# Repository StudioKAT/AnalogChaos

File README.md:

# Analog Chaos

## 概要 / Overview

**Analog Chaos**は、2HPサイズの電圧制御可能なJerk Chaos CVジェネレーターです。

アナログ回路のフィードバックが生み出す、決定論的でありながら不規則な変化が特徴です。パッチに「偶然のようで、どこか連続性のある」揺らぎを加えます。

相互に関連しながら異なる表情を見せるX・Y・Zの3つのCV出力を搭載。複数のパラメーターを同時に変調することで、つながりのある複雑な動きを作り出せます。

変化の速度はRateノブと外部CVで調整でき、超低速域からLFO領域まで対応します。ゆっくりと移り変わる音色から、不規則なうねりまで、幅広いモジュレーションに活用できます。

基板上には、動きの性質を調整する4つの半固定抵抗を備えています。  
- Damp：振動を抑える帰還の強さを調整します。動きの勢いや収まり方に関わります。
- Gain：信号を回路へ戻す帰還の利得を調整します。出力音量ではなく、カオスを生み出すループの働きに関わります。
- Mod：回路内部に加える直流バイアスを調整します。動作の中心をずらすことで、揺らぎの偏りや動き方を変化させます。
- NL Drive：ダイオードによる非線形帰還の強さを調整します。波形の折れ曲がり方や、不規則な動きの生じ方に関わります。

これらは互いに影響し合い、設定によって不規則な揺らぎから周期的な動き、変化が収まる状態まで、振る舞いが変化します。

---

**Analog Chaos** is a voltage-controlled jerk chaos CV generator in a compact 2HP Eurorack format.

Feedback within its analog circuitry produces behavior that is deterministic yet irregular, adding fluctuations to your patch that feel unpredictable while retaining a sense of continuity.

Three CV outputs—X, Y, and Z—provide distinct but interrelated signals. Modulate multiple parameters simultaneously to create complex, connected movement throughout your patch.

The Rate knob and external CV input control the speed of these changes, covering a range from ultra-slow movement to LFO rates. From gradually evolving timbres to irregular swells, Analog Chaos offers a wide range of modulation possibilities.

Four trimmers on the circuit board let you adjust the character of the movement:

- **Damp:** Adjusts the strength of the feedback that damps oscillation, influencing how vigorously the circuit moves and how its motion settles.
- **Gain:** Adjusts the gain of the feedback loop that generates chaos, shaping the circuit’s behavior rather than directly setting the output level.
- **Mod:** Adjusts an internal DC bias, shifting the circuit’s operating point to change the balance and character of its fluctuations.
- **NL Drive:** Adjusts the strength of the nonlinear feedback through the diodes, influencing how the waveform bends and how irregular movement develops.

These controls interact with one another. Depending on their settings, the circuit can move between chaotic fluctuations, periodic oscillation, and a settled state.

## 仕様 / Spec
- Format: Eurorack
- Function: Chaos
- Current needs: +12V: 25mA, -12V: 25mA
- Width: 2 HP
- Depth: 36mm (including power connector)

## 販売 / Sales

StudioKATオフィシャルショップで販売しています。(日本国内限定)  
https://www.studiokat.jp/items/164466150

## ライセンス / License

この作品は [Creative Commons 表示 - 継承 4.0 国際 (CC BY-SA 4.0)](https://creativecommons.org/licenses/by-sa/4.0/deed.ja) の下でライセンスされています。  
This work is licensed under the [Creative Commons Attribution-ShareAlike 4.0 International License](https://creativecommons.org/licenses/by-sa/4.0/).

## クレジット / Credits

- Designed by : StudioKAT
- Website : https://www.studiokat.jp/
- GitHub : https://github.com/StudioKAT
- X(Twitter) : https://x.com/StudioKAT_synth
- Instagram : https://www.instagram.com/studiokat_modular/

## 更新履歴 / Changelog

- `2026-10-30` v2.0 Released version 2.0
- `2026-07-05` v1.0 Released version 1.0

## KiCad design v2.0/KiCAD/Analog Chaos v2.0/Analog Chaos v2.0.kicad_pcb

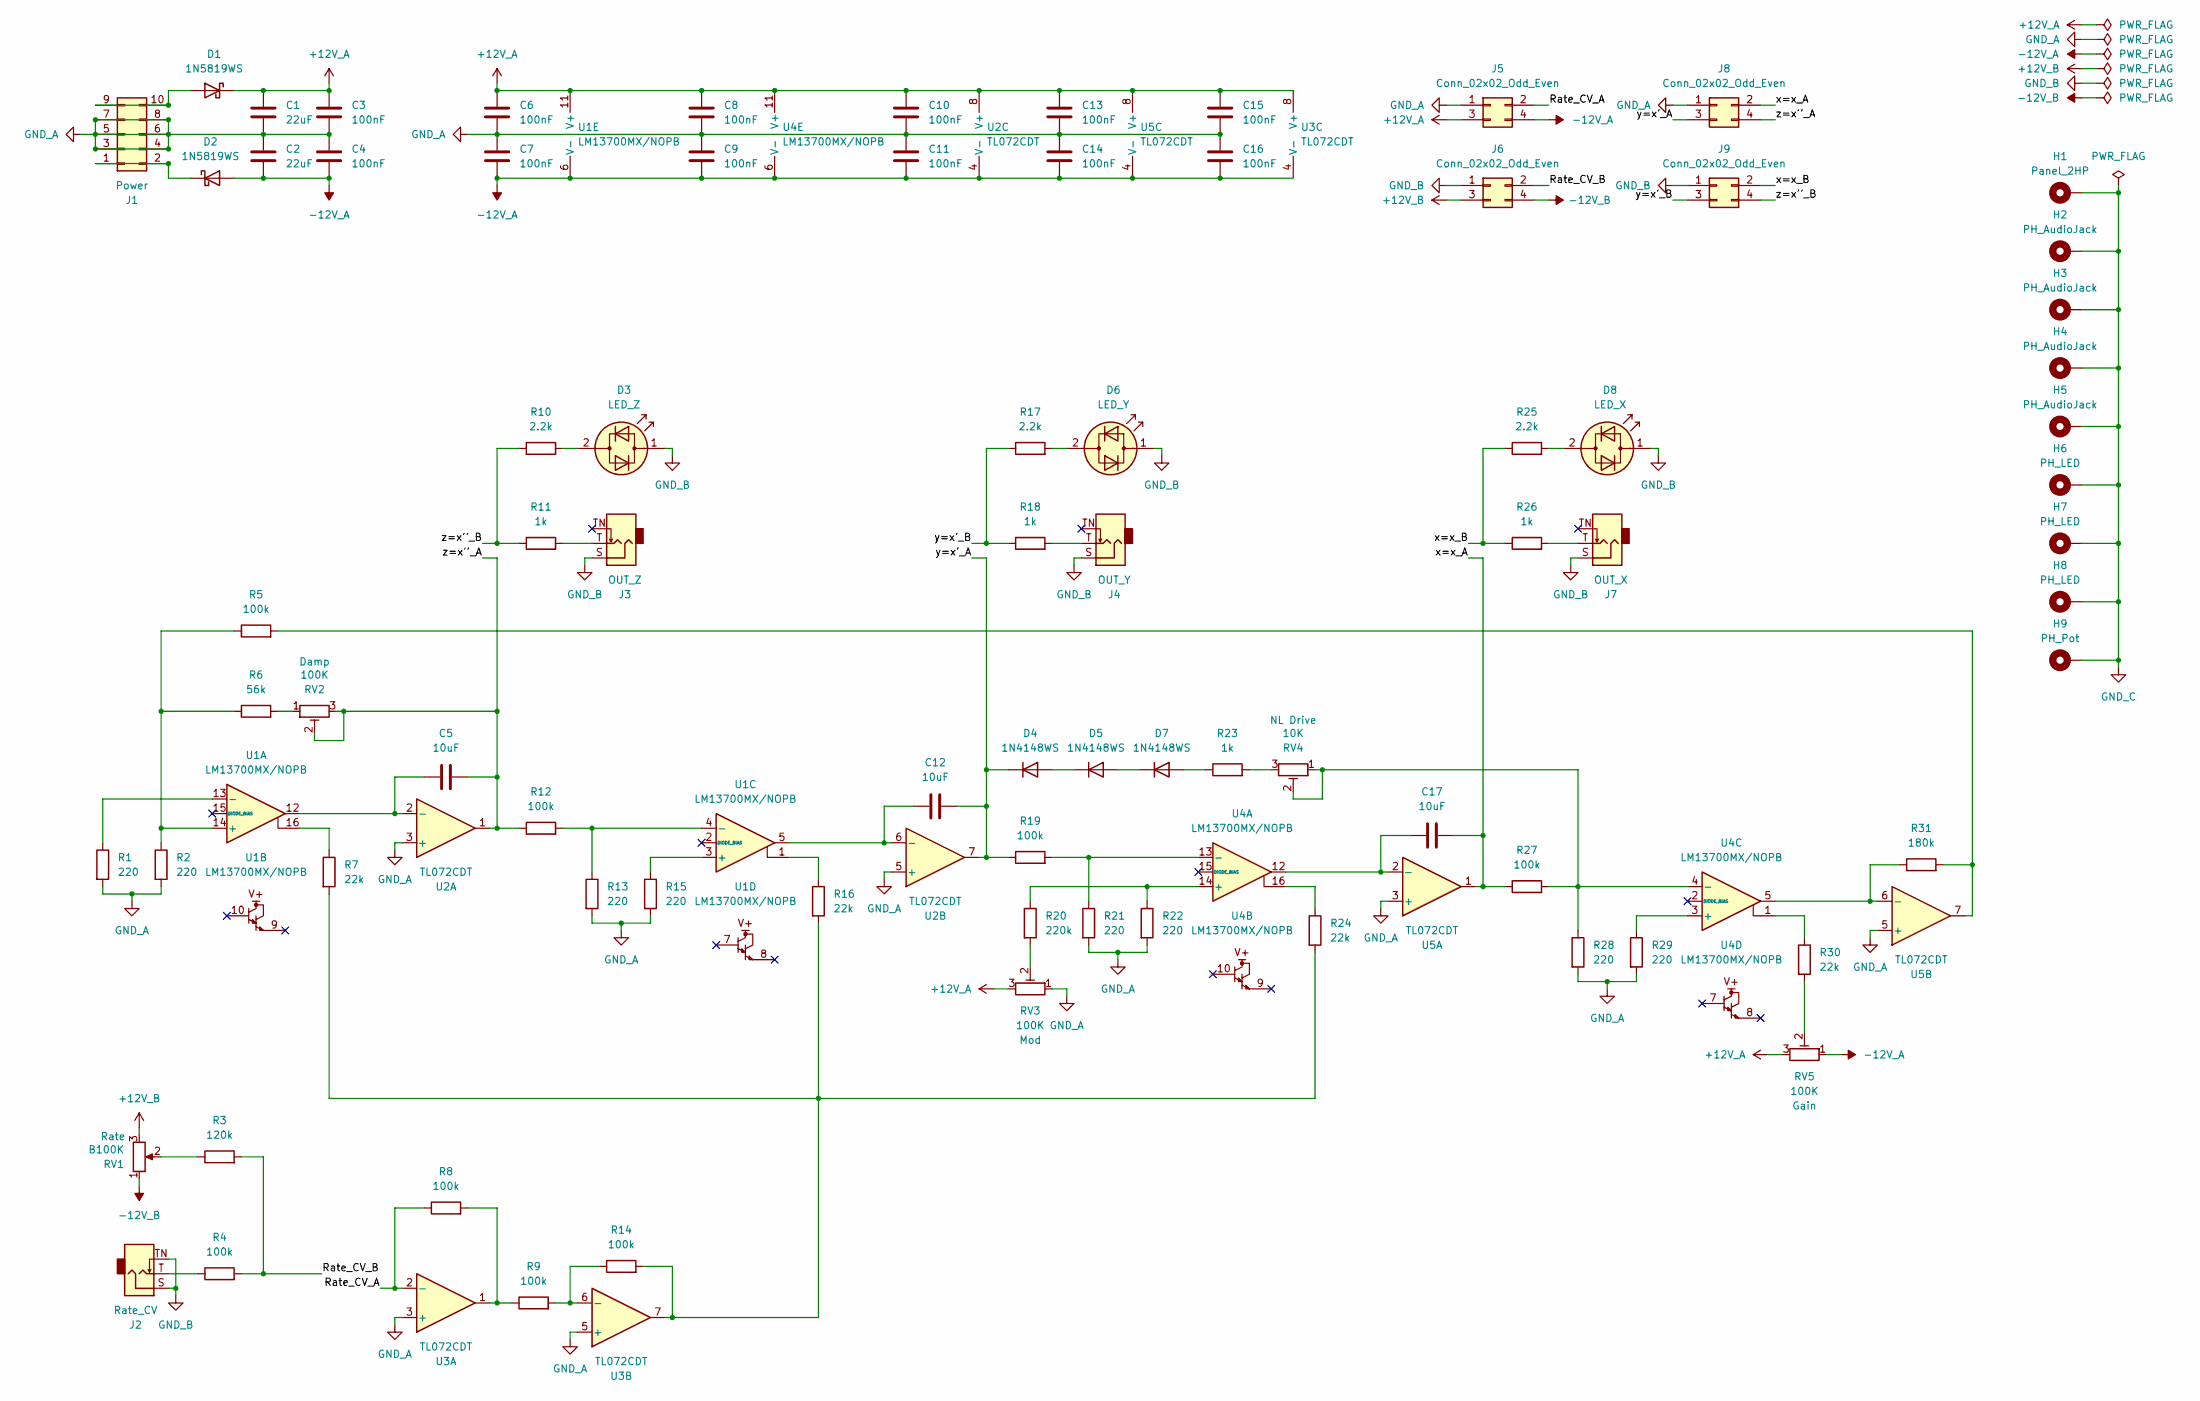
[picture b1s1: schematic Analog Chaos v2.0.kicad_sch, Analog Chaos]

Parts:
C1, C2: 22uF; C_0805_2012Metric; Voltage 25V; Tolerance ±20%; MFR Part CL21A226MAQNNNE; JLC Type Basic
C3, C4, C6, C7, C8, C9, C10, C11, C13, C14, C15, C16: 100nF; C_0603_1608Metric; Voltage 50V; Tolerance ±10%; MFR Part CC0603KRX7R9BB104; JLC Type Basic
C5, C12, C17: 10uF; C_0603_1608Metric; Voltage 25V; Tolerance ±20%; MFR Part CL10A106MA8NRNC; JLC Type Basic
D1, D2: 1N5819WS; D_SOD-323; MFR Part 1N5819WS; JLC Type Basic
D3: LED_Z; LED_D3.0mm_Clear
D4, D5, D7: 1N4148WS; D_SOD-323; MFR Part 1N4148WS; JLC Type Basic
D6: LED_Y; LED_D3.0mm_Clear
D8: LED_X; LED_D3.0mm_Clear
H1: Panel_2HP
H2, H3, H4, H5: PH_AudioJack; PH_AudioJack_3.5mm_Pad
H6, H7, H8: PH_LED; PH_LED_3.0mm_Pad
H9: PH_Pot; PH_RV09
J1: Power; IDC-Header_2x05_P2.54mm_Horizontal_SMD_EuroPower
J2: Rate_CV; Jack_3.5mm_QingPu_WQP-PJ398SM
J3: OUT_Z; Jack_3.5mm_QingPu_WQP-PJ398SM
J4: OUT_Y; Jack_3.5mm_QingPu_WQP-PJ398SM
J5, J8: Conn_02x02_Odd_Even; PinHeader_2x02_P2.54mm_Stand_SMD
J6, J9: Conn_02x02_Odd_Even; PinHeader_2x02_P2.54mm_Vertical_SMD
J7: OUT_X; Jack_3.5mm_QingPu_WQP-PJ398SM
R1, R2, R13, R15, R21, R22, R28, R29: 220; R_0603_1608Metric; Tolerance ±1%; MFR Part 0603WAF2200T5E; JLC Type Basic
R3: 120k; R_0603_1608Metric; Tolerance ±1%; MFR Part 0603WAF1203T5E; JLC Type Basic
R4, R5, R8, R9, R12, R14, R19, R27: 100k; R_0603_1608Metric; Tolerance ±1%; MFR Part 0603WAF1003T5E; JLC Type Basic
R6: 56k; R_0603_1608Metric; Tolerance ±1%; MFR Part 0603WAF5602T5E; JLC Type Basic
R7, R16, R24, R30: 22k; R_0603_1608Metric; Tolerance ±1%; MFR Part 0603WAF2202T5E; JLC Type Basic
R10, R17, R25: 2.2k; R_0603_1608Metric; Tolerance ±1%; MFR Part 0603WAF2201T5E; JLC Type Basic
R11, R18, R23, R26: 1k; R_0603_1608Metric; Tolerance ±1%; MFR Part 0603WAF1001T5E; JLC Type Basic
R20: 220k; R_0603_1608Metric; Tolerance ±1%; MFR Part 0603WAF2203T5E; JLC Type Basic
R31: 180k; R_0603_1608Metric; Tolerance ±1%; MFR Part 0603WAF1803T5E; LCSC C22827
RV1: B100K; Potentiometer_RV09
RV2, RV3, RV5: 100K; Potentiometer_Vishay_T73YP_Vertical
RV4: 10K; Potentiometer_Vishay_T73YP_Vertical
U1, U4: LM13700MX/NOPB; SOIC-16_3.9x9.9mm_P1.27mm; LCSC C174050
U2, U3, U5: TL072CDT; SOIC-8_3.9x4.9mm_P1.27mm; MFR Part TL072CDT; JLC Type Basic

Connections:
+12V_A: C1.1, C3.1, C6.1, C8.1, C10.1, C13.1, C15.1, D1.1 (K), J5.3, RV3.3, RV5.3, U1.11 (V+), U2.8 (V+), U3.8 (V+), U4.11 (V+), U5.8 (V+)
+12V_B: J6.3, RV1.3
-12V_A: C2.2, C4.2, C7.2, C9.2, C11.2, C14.2, C16.2, D2.2 (A), J5.4, RV5.1, U1.6 (V-), U2.4 (V-), U3.4 (V-), U4.6 (V-), U5.4 (V-)
-12V_B: J6.4, RV1.1
/Rate_CV_A: J5.2, R8.1, U3.2 (-)
/Rate_CV_B: J6.2, R3.2, R4.2
/x=x_A: C17.2, J8.2, R27.1, U5.1
/x=x_B: J9.2, R25.1, R26.1
/y=x'_A: C12.2, D4.1 (K), J8.3, R19.1, U2.7
/y=x'_B: J9.3, R17.1, R18.1
/z=x''_A: C5.2, J8.4, R12.1, RV2.2, RV2.3, U2.1
/z=x''_B: J9.4, R10.1, R11.1
GND_A: C1.2, C2.1, C3.2, C4.1, C6.2, C7.1, C8.2, C9.1, C10.2, C11.1, C13.2, C14.1, C15.2, C16.1, J1.3, J1.4, J1.5, J1.6, J1.7, J1.8, J5.1, J8.1, R1.2, R2.2, R13.2, R15.2, R21.2, R22.2, R28.2, R29.2, RV3.1, U2.3 (+), U2.5 (+), U3.3 (+), U3.5 (+), U5.3 (+), U5.5 (+)
GND_B: D3.1 (KA), D6.1 (KA), D8.1 (KA), J2.S, J2.TN, J3.S, J4.S, J6.1, J7.S, J9.1
GND_C: H1.1 (1_1), H2.1 (1_1), H3.1 (1_1), H4.1 (1_1), H5.1 (1_1), H6.1 (1_1), H7.1 (1_1), H8.1 (1_1), H9.1 (1_1)
unnamed: D1.2 (A), J1.9, J1.10
unnamed: D2.1 (K), J1.1, J1.2
unnamed: D3.2 (AK), R10.2
unnamed: D4.2 (A), D5.1 (K)
unnamed: D5.2 (A), D7.1 (K)
unnamed: D6.2 (AK), R17.2
unnamed: D7.2 (A), R23.1
unnamed: D8.2 (AK), R25.2
unnamed: J2.T, R4.1
unnamed: J3.T, R11.2
unnamed: J4.T, R18.2
unnamed: J7.T, R26.2
unnamed: R3.1, RV1.2
unnamed: R6.2, RV2.1
unnamed: R7.1, U1.16
unnamed: R8.2, R9.1, U3.1
unnamed: R7.2, R14.2, R16.2, R24.2, U3.7
unnamed: R16.1, U1.1
unnamed: R20.2, RV3.2
unnamed: R23.2, RV4.3
unnamed: R24.1, U4.16
unnamed: R30.1, U4.1
unnamed: R30.2, RV5.2
unnamed: R5.2, R31.2, U5.7
unnamed: R2.1, R5.1, R6.1, U1.14 (+)
unnamed: R1.1, U1.13 (-)
unnamed: R15.1, U1.3 (+)
unnamed: R12.2, R13.1, U1.4 (-)
unnamed: C5.1, U1.12, U2.2 (-)
unnamed: C12.1, U1.5, U2.6 (-)
unnamed: R9.2, R14.1, U3.6 (-)
unnamed: R20.1, R22.1, U4.14 (+)
unnamed: R19.2, R21.1, U4.13 (-)
unnamed: R29.1, U4.3 (+)
unnamed: R27.2, R28.1, RV4.1, RV4.2, U4.4 (-)
unnamed: C17.1, U4.12, U5.2 (-)
unnamed: R31.1, U4.5, U5.6 (-)

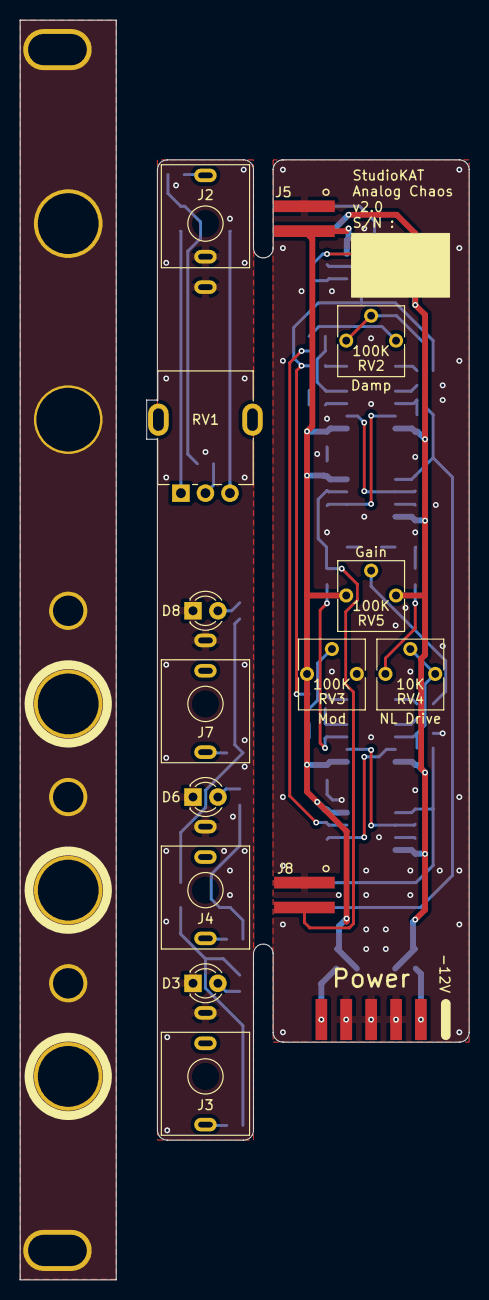
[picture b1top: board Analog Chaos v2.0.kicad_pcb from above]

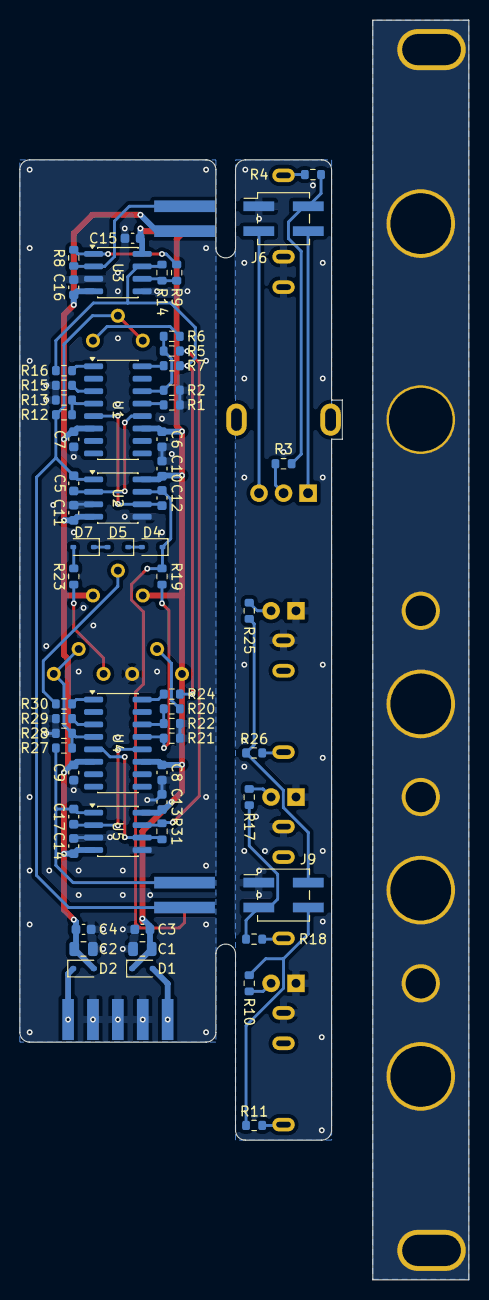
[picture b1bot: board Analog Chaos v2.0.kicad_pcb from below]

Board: 2 copper layers, 32.9 x 100.0 mm, 84 parts (60 on the bottom side), 52 nets.

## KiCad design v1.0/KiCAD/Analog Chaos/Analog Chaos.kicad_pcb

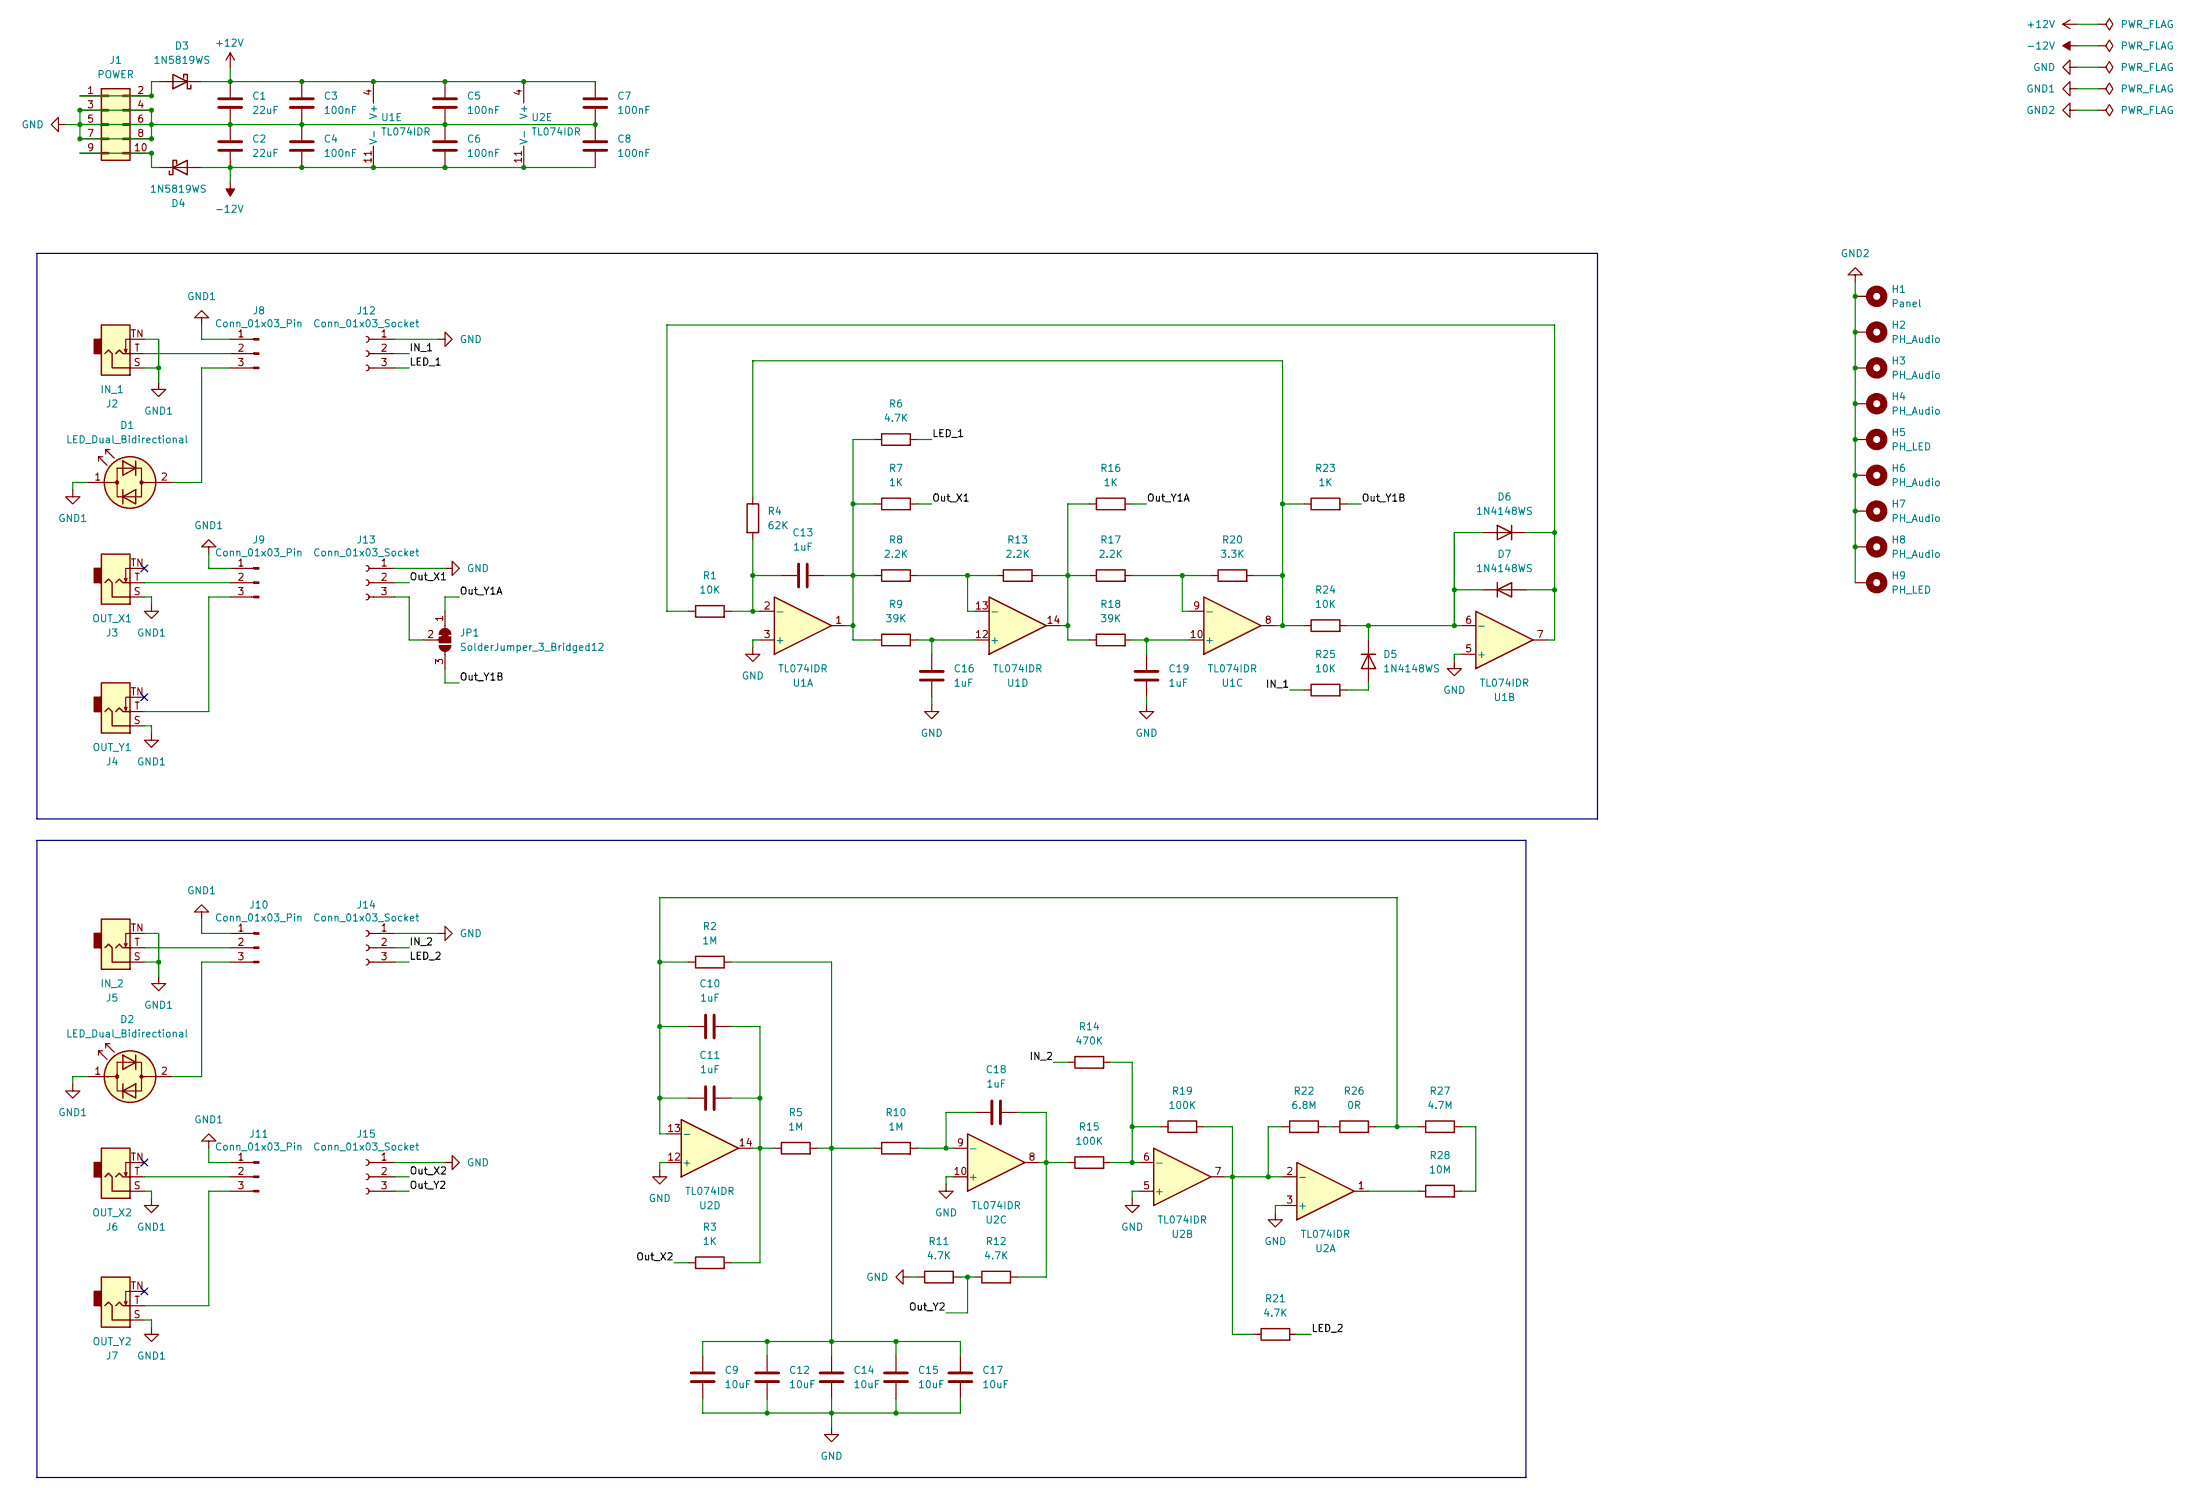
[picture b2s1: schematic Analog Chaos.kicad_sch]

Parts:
C1, C2: 22uF; C_0805_2012Metric; LCSC C45783
C3, C4, C5, C6, C7, C8: 100nF; C_0603_1608Metric; LCSC C14663
C9, C12, C14, C15, C17: 10uF; C_0603_1608Metric; LCSC C96446
C10, C11, C13, C16, C18, C19: 1uF; C_0603_1608Metric; LCSC C15849
D1, D2: LED_Dual_Bidirectional; LED_D3.0mm_Clear
D3, D4: 1N5819WS; D_SOD-323; LCSC C64886
D5, D6, D7: 1N4148WS; D_SOD-323; LCSC C2128
H1: Panel; Panel_2HP
H2, H3, H4, H6, H7, H8: PH_Audio; PH_AudioJack_3.5mm_Pad
H5, H9: PH_LED; PH_LED_3.0mm_Pad
J1: POWER; PinHeader_2x05_2.54mm_Europower
J2: IN_1; AudioJack_PJ301M-12
J3: OUT_X1; AudioJack_PJ301M-12
J4: OUT_Y1; AudioJack_PJ301M-12
J5: IN_2; AudioJack_PJ301M-12
J6: OUT_X2; AudioJack_PJ301M-12
J7: OUT_Y2; AudioJack_PJ301M-12
J8, J9, J10, J11: Conn_01x03_Pin; PinHeader_1x03_P2.54mm_Vertical
J12, J13, J14, J15: Conn_01x03_Socket; PinSocket_1x03_P2.54mm_Vertical
JP1: SolderJumper_3_Bridged12; SolderJumper-3_P1.3mm_Bridged12_RoundedPad1.0x1.5mm
R1, R24, R25: 10K; R_0603_1608Metric; LCSC C25804
R2, R5, R10: 1M; R_0603_1608Metric; LCSC C22935
R3, R7, R16, R23: 1K; R_0603_1608Metric; LCSC C21190
R4: 62K; R_0603_1608Metric; LCSC C23221
R6, R11, R12, R21: 4.7K; R_0603_1608Metric; LCSC C23162
R8, R13, R17: 2.2K; R_0603_1608Metric; LCSC C4190
R9, R18: 39K; R_0603_1608Metric; LCSC C23153
R14: 470K; R_0603_1608Metric; LCSC C23178
R15, R19: 100K; R_0603_1608Metric; LCSC C25803
R20: 3.3K; R_0603_1608Metric; LCSC C22978
R22: 6.8M; R_0603_1608Metric; LCSC C23213
R26: 0R; R_0603_1608Metric; LCSC C21189
R27: 4.7M; R_0603_1608Metric; LCSC C23163
R28: 10M; R_0603_1608Metric; LCSC C7250
U1, U2: TL074IDR; SOIC-14_3.9x8.7mm_P1.27mm; LCSC C6964

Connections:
+12V: C1.1, C3.1, C5.1, C7.1, D3.1 (K), U1.4 (V+), U2.4 (V+)
-12V: C2.2, C4.2, C6.2, C8.2, D4.2 (A), U1.11 (V-), U2.11 (V-)
/IN_1: J12.2, R25.1
/IN_2: J14.2, R14.1
/LED_1: J12.3, R6.2
/LED_2: J14.3, R21.2
/Out_X1: J13.2, R7.2
/Out_X2: J15.2, R3.1
/Out_Y1A: JP1.1 (A), R16.2
/Out_Y1B: JP1.3 (B), R23.2
/Out_Y2: J15.3, R11.2, R12.1
GND: C1.2, C2.1, C3.2, C4.1, C5.2, C6.1, C7.2, C8.1, C9.2, C12.2, C14.2, C15.2, C16.2, C17.2, C19.2, J1.3, J1.4, J1.5, J1.6, J1.7, J1.8, J12.1, J13.1, J14.1, J15.1, R11.1, U1.3 (+), U1.5 (+), U2.3 (+), U2.5 (+), U2.10 (+), U2.12 (+)
GND1: D1.1 (KA), D2.1 (KA), J2.S, J2.TN, J3.S, J4.S, J5.S, J5.TN, J6.S, J7.S, J8.1, J9.1, J10.1, J11.1
GND2: H1.1 (1_1), H2.1 (1_1), H3.1 (1_1), H4.1 (1_1), H5.1 (1_1), H6.1 (1_1), H7.1 (1_1), H8.1 (1_1), H9.1 (1_1)
unnamed: C10.2, C11.2, R3.2, R5.1, U2.14
unnamed: C9.1, C12.1, C14.1, C15.1, C17.1, R2.2, R5.2, R10.1
unnamed: C13.2, R6.1, R7.1, R8.1, R9.1, U1.1
unnamed: C18.2, R12.2, R15.1, U2.8
unnamed: D1.2 (AK), J8.3
unnamed: D2.2 (AK), J10.3
unnamed: D3.2 (A), J1.1, J1.2
unnamed: D4.1 (K), J1.9, J1.10
unnamed: D5.2 (A), R25.2
unnamed: D5.1 (K), D6.2 (A), D7.1 (K), R24.2, U1.6 (-)
unnamed: D6.1 (K), D7.2 (A), R1.1, U1.7
unnamed: J2.T, J8.2
unnamed: J3.T, J9.2
unnamed: J4.T, J9.3
unnamed: J5.T, J10.2
unnamed: J6.T, J11.2
unnamed: J7.T, J11.3
unnamed: J13.3, JP1.2 (C)
unnamed: R13.2, R16.1, R17.1, R18.1, U1.14
unnamed: R4.1, R20.2, R23.1, R24.1, U1.8
unnamed: R22.2, R26.1
unnamed: R27.2, R28.2
unnamed: R28.1, U2.1
unnamed: C13.1, R1.2, R4.2, U1.2 (-)
unnamed: C19.1, R18.2, U1.10 (+)
unnamed: R17.2, R20.1, U1.9 (-)
unnamed: C16.1, R9.2, U1.12 (+)
unnamed: R8.2, R13.1, U1.13 (-)
unnamed: R19.2, R21.1, R22.1, U2.2 (-), U2.7
unnamed: R14.2, R15.2, R19.1, U2.6 (-)
unnamed: C18.1, R10.2, U2.9 (-)
unnamed: C10.1, C11.1, R2.1, R26.2, R27.1, U2.13 (-)

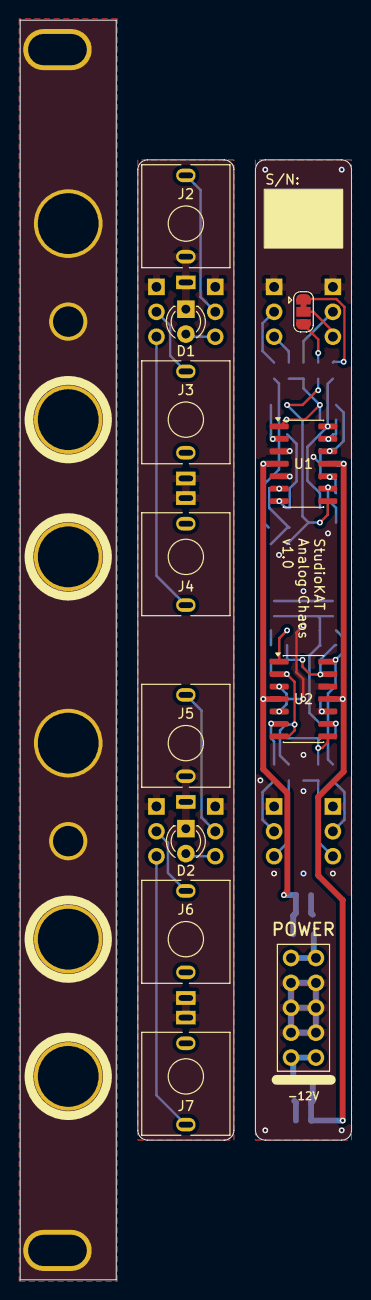
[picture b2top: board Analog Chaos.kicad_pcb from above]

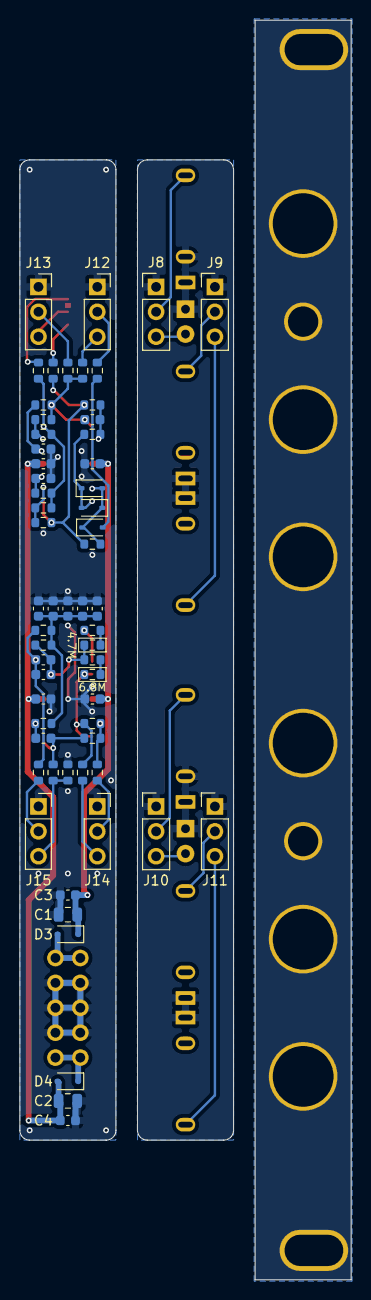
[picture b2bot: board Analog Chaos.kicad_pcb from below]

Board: 2 copper layers, 33.8 x 128.5 mm, 81 parts (60 on the bottom side), 46 nets.
